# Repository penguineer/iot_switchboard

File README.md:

# iot_switchboard Rev. 2 (Tapper)

Breadkout board for 2 Digitast switches with I2C/Interrupt connection

## Features:
* Suitable for up to 2 Digitast switches with or without LED (they come in various colors)
* Configurable for detection of click, double-click and hold
* Configurable LED behavior
* integrated µC takes care of debounce and I2C communication
* I2C address selectable by solder bridges
* Interrupt line tells when there is an event, so no polling necessary

Open source software and hardware!

## State of the project
  * Rev 2 PCB has been sucessfully tested
  * Open: Write firmware (there are reliable and tested debouncing algorithms, though)
  * Open: Setup and Test jig

## Get the Board
You can order the [Revision 2 Board from Oshpark](https://oshpark.com/shared_projects/GlxIHXRd/)

**Note:** QFN20 package

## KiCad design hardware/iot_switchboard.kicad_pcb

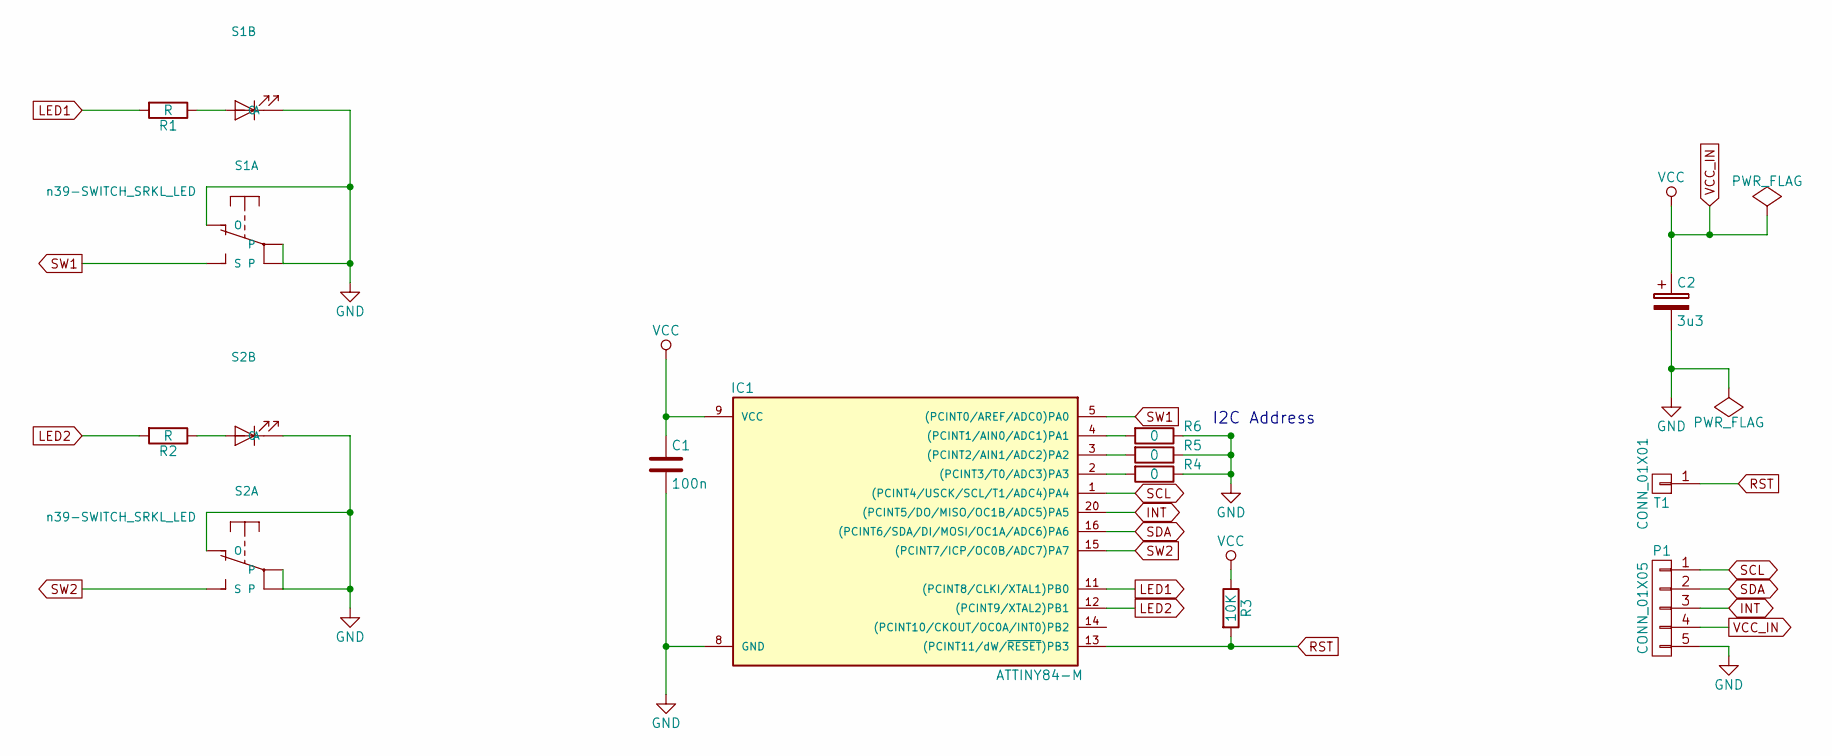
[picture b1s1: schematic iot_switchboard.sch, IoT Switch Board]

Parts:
C1: 100n; C_0603_HandSoldering
C2: 3u3; C_0603_HandSoldering
IC1: ATTINY84-M; QFN-20-1EP_4x4mm_Pitch0.5mm
P1: CONN_01X05; Pin_Header_Straight_1x05
R1, R2: R; Resistor_SMD+THTuniversal_0805to1206_RM10_HandSoldering
R3: 10K; R_0603_HandSoldering
R4, R5, R6: 0; R_0402
S1, S2: n39-SWITCH_SRKL_LED
T1: CONN_01X01; Measurement_Point_Round-TH_Small

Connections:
GND: C1.2, C2.2, IC1.8 (GND), P1.5, R4.1, R5.1, R6.1, S1.2, S1.3, S1.4 (O), S1.- (C), S2.2, S2.3, S2.4 (O), S2.- (C)
INT: IC1.20 ((PCINT5/DO/MISO/OC1B/ADC5)PA5), P1.3
LED1: IC1.11 ((PCINT8/CLKI/XTAL1)PB0), R1.2
LED2: IC1.12 ((PCINT9/XTAL2)PB1), R2.2
unnamed: IC1.2 ((PCINT3/T0/ADC3)PA3), R4.2
unnamed: IC1.3 ((PCINT2/AIN1/ADC2)PA2), R5.2
unnamed: IC1.4 ((PCINT1/AIN0/ADC1)PA1), R6.2
unnamed: R1.1, S1.+ (A)
unnamed: R2.1, S2.+ (A)
RST: IC1.13 ((PCINT11/dW/~RESET~)PB3), R3.2, T1.1
SCL: IC1.1 ((PCINT4/USCK/SCL/T1/ADC4)PA4), P1.1
SDA: IC1.16 ((PCINT6/SDA/DI/MOSI/OC1A/ADC6)PA6), P1.2
SW1: IC1.5 ((PCINT0/AREF/ADC0)PA0), S1.1 (S)
SW2: IC1.15 ((PCINT7/ICP/OC0B/ADC7)PA7), S2.1 (S)
VCC_IN: C1.1, C2.1, IC1.9 (VCC), P1.4, R3.1

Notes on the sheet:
I2C Address

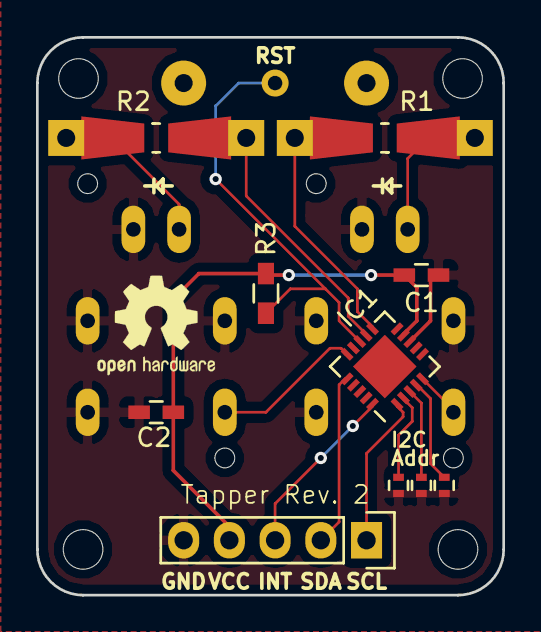
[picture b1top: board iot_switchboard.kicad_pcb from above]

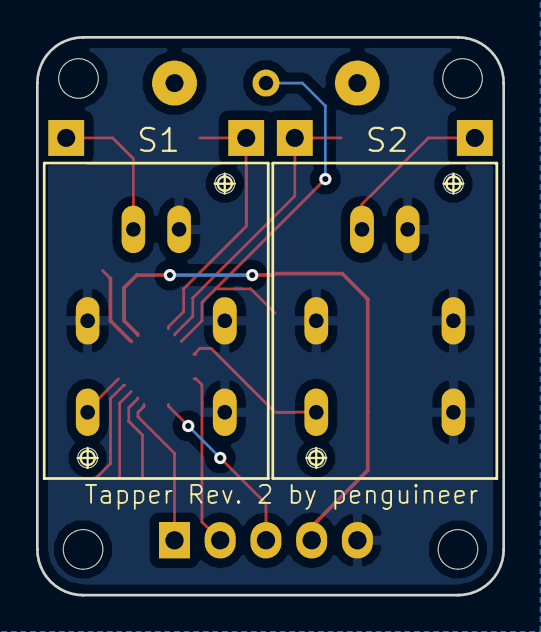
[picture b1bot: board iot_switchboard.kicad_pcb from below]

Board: 2 copper layers, 25.9 x 31.0 mm, 13 parts (2 on the bottom side), 15 nets.

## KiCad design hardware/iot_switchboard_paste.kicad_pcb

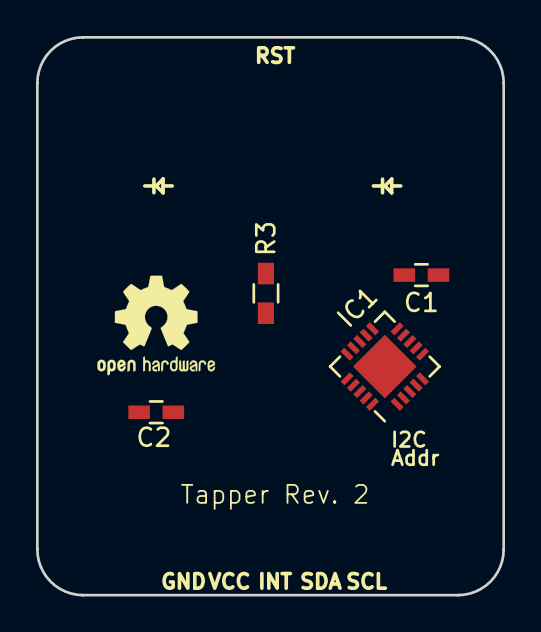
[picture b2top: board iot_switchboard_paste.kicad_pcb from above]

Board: 2 copper layers, 25.9 x 31.0 mm, 4 parts (0 on the bottom side), 3 nets, no tracks yet.

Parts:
C1: 100n; C_0603_HandSoldering
C2: 3u3; C_0603_HandSoldering
IC1: ATTINY84-M; QFN-20-1EP_4x4mm_Pitch0.5mm
R3: 10K; R_0603_HandSoldering

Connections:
GND: C1.2, C2.2, IC1.8
RST: IC1.13, R3.2
VCC_IN: C1.1, C2.1, IC1.9, R3.1

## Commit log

2017-03-18 KiCad gitignore for hardware folder
2017-03-18 layout and attiny in QFN20
2017-03-18 first hardware revision: schematic and started layout
2017-03-21 Adapt to Oshpark design rules
2017-04-14 Replace load capacitor by 0603 type
2017-04-14 Reduce to 2 switches and adapt outline
2017-04-15 New Layout
    Yeah!
2017-04-15 Copy the board with only pre-populated compontens
    Needed for the solder mask
2017-04-17 Update the Readme to the current project state
2018-09-05 Update project status and new images
